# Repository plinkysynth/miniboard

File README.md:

# miniboard - a super minimal fatar tp9 37 key keybed scanner using an rp2040 mcu by @mmalex.bsky.social

August 2026

## the keybed wot you need

there's no point looking at this project until you are the proud owner of a fatar 9s keybed. probably the 37 key variant. 

- the keybed - https://www.fatar.com/products/tp9s/
- datasheet - https://www.antonus-synths.com/enlo-1/fatar/DataSheet-TP9S%2BP.pdf

I got mine at great expense a few years ago from
https://enlo-1.com/products/fatar-tp-9s-keyboard
but im not sure if they are meant to sell them to us hobbyists? either way it was expensive for what it is! maybe you can find one cheaper somewhere else. I am not affiliated with them in any way, just documenting my build.

## whence came this mess

forked from my earlier 2024 zacboard project, that included an oled, 2 encoders, and a silly set of i2c slider boards that allowed it to sport more sliders than keys.

im not sure if i ever released that one publically (* i did not), but i was curious about making a super minimal 'fatar keybed and nothing else' the other day, so I stripped everything down, speed-designed a PCB, and re-ordered from JLC. the boards just arrived, they work, I am putting this up on github before thinking too much...

## software

the software just times make/breaks when scanning the keybed, as one must, and uses that to pick a velocity.

it also feeds the aftertouch resistor to ADC0 and uses that to generate aftertouch events.

it sends MIDI messages out on channel 0 on the TRS port and over usb midi. 

the pcb has a 3 pin connector for a raspberry pi debug probe 

https://www.raspberrypi.com/products/debug-probe/

which I highly recommend for all rp2040 hacking projects. it gives you quick way to flash new software without messing with reset buttons, clean debugging in vscode, watch, breakpoints, etc.

i set this project to use rtt segger style printf, which is THE ONE TRUE WAY but is surprisingly underdocumented in the pico sdk. If you have a probe connected you can
see your printf's in vscode via the TERMINAL tab, and its really cheap, and doesnt tie up the USB port or a 
serial port, nor use any GPIOs. lovely!

## hardware

power is over usb-c obviously

i did this in a yolo rush, so its a bit rough.
ordering your own pcbs, its the usual kicad -> jlcpcb -> yay!
I even left the production files checked in, so you could even just upload those straight to JLC. it worked for me, but see the section below on improvements you might want to make before spending money.

all the parts should be readily available via their assembly service.

I accept no responsibility for anything that may come from building this stuff! you're on your own.

## mounting

the open scad file is for a simple plank to screw onto the keybed and mount the circuit board.

a plank of wood or other material would be nicer.

i screwed it into the keybed with 8 wood screws i found in a cupboard :) M3 or M4 I think they were.
the pcb has two m3 holes in it, which I used 2 M3 machine screws and nuts for. the stl/openscad file has holes for these.

## keybed connector

i HATE HATE HATE the minimatch connector that fatar uses, but here we are. you need some 20 way
ribbon cable to clamp it onto, which requires FORCE which often breaks the fragile plastic.
I got the connectors from digikey:

| use | quantity | digikey part | manufacturer | manufacturer part | description |
| --- | ---: | --- | --- | --- | --- |
| for the cable... | 2x | A99456CT-ND | TE CONNECTIVITY AMP (VA) | 9-215083-0 | CONN PLUG 20POS IDC 28AWG TIN |
| for the pcb... | 1x | A99465CT-ND | TE CONNECTIVITY AMP (VA) | 9-215079-0 | CONN RCPT 20POS 0.1 TIN PCB |

and standard 28AWG 20 way ribbon cable.

The keybed also has a little flat flex variable resistor. connect two wires to it
and solder them to the outer two pins of the 4 pin connector on the pcb. voila,
after touch.

## PCB design mistakes chapter:

* i should have connected the last 2 pins to GPIOs. I didn't. as a result you can't scan larger keyboards.
If i was ordering from JLCPCB again, I'd hook up those two not connected pins to GPIOs.

* the TRS jack for midi is too close to the USB-C. it works, but its close.

* obviously it could sprout more connections, encoders, buttons, etc.... but that wasnt the point of 
this minimalist project.  

* it would make sense to expose more of the free GPIOs as testpads or connectors or whatnot.

* the routing is fine, honest.

## license

released into as liberal a license as I can: [CC0](LICENSE.md)...

- alex 'mmalex' evans august 2026

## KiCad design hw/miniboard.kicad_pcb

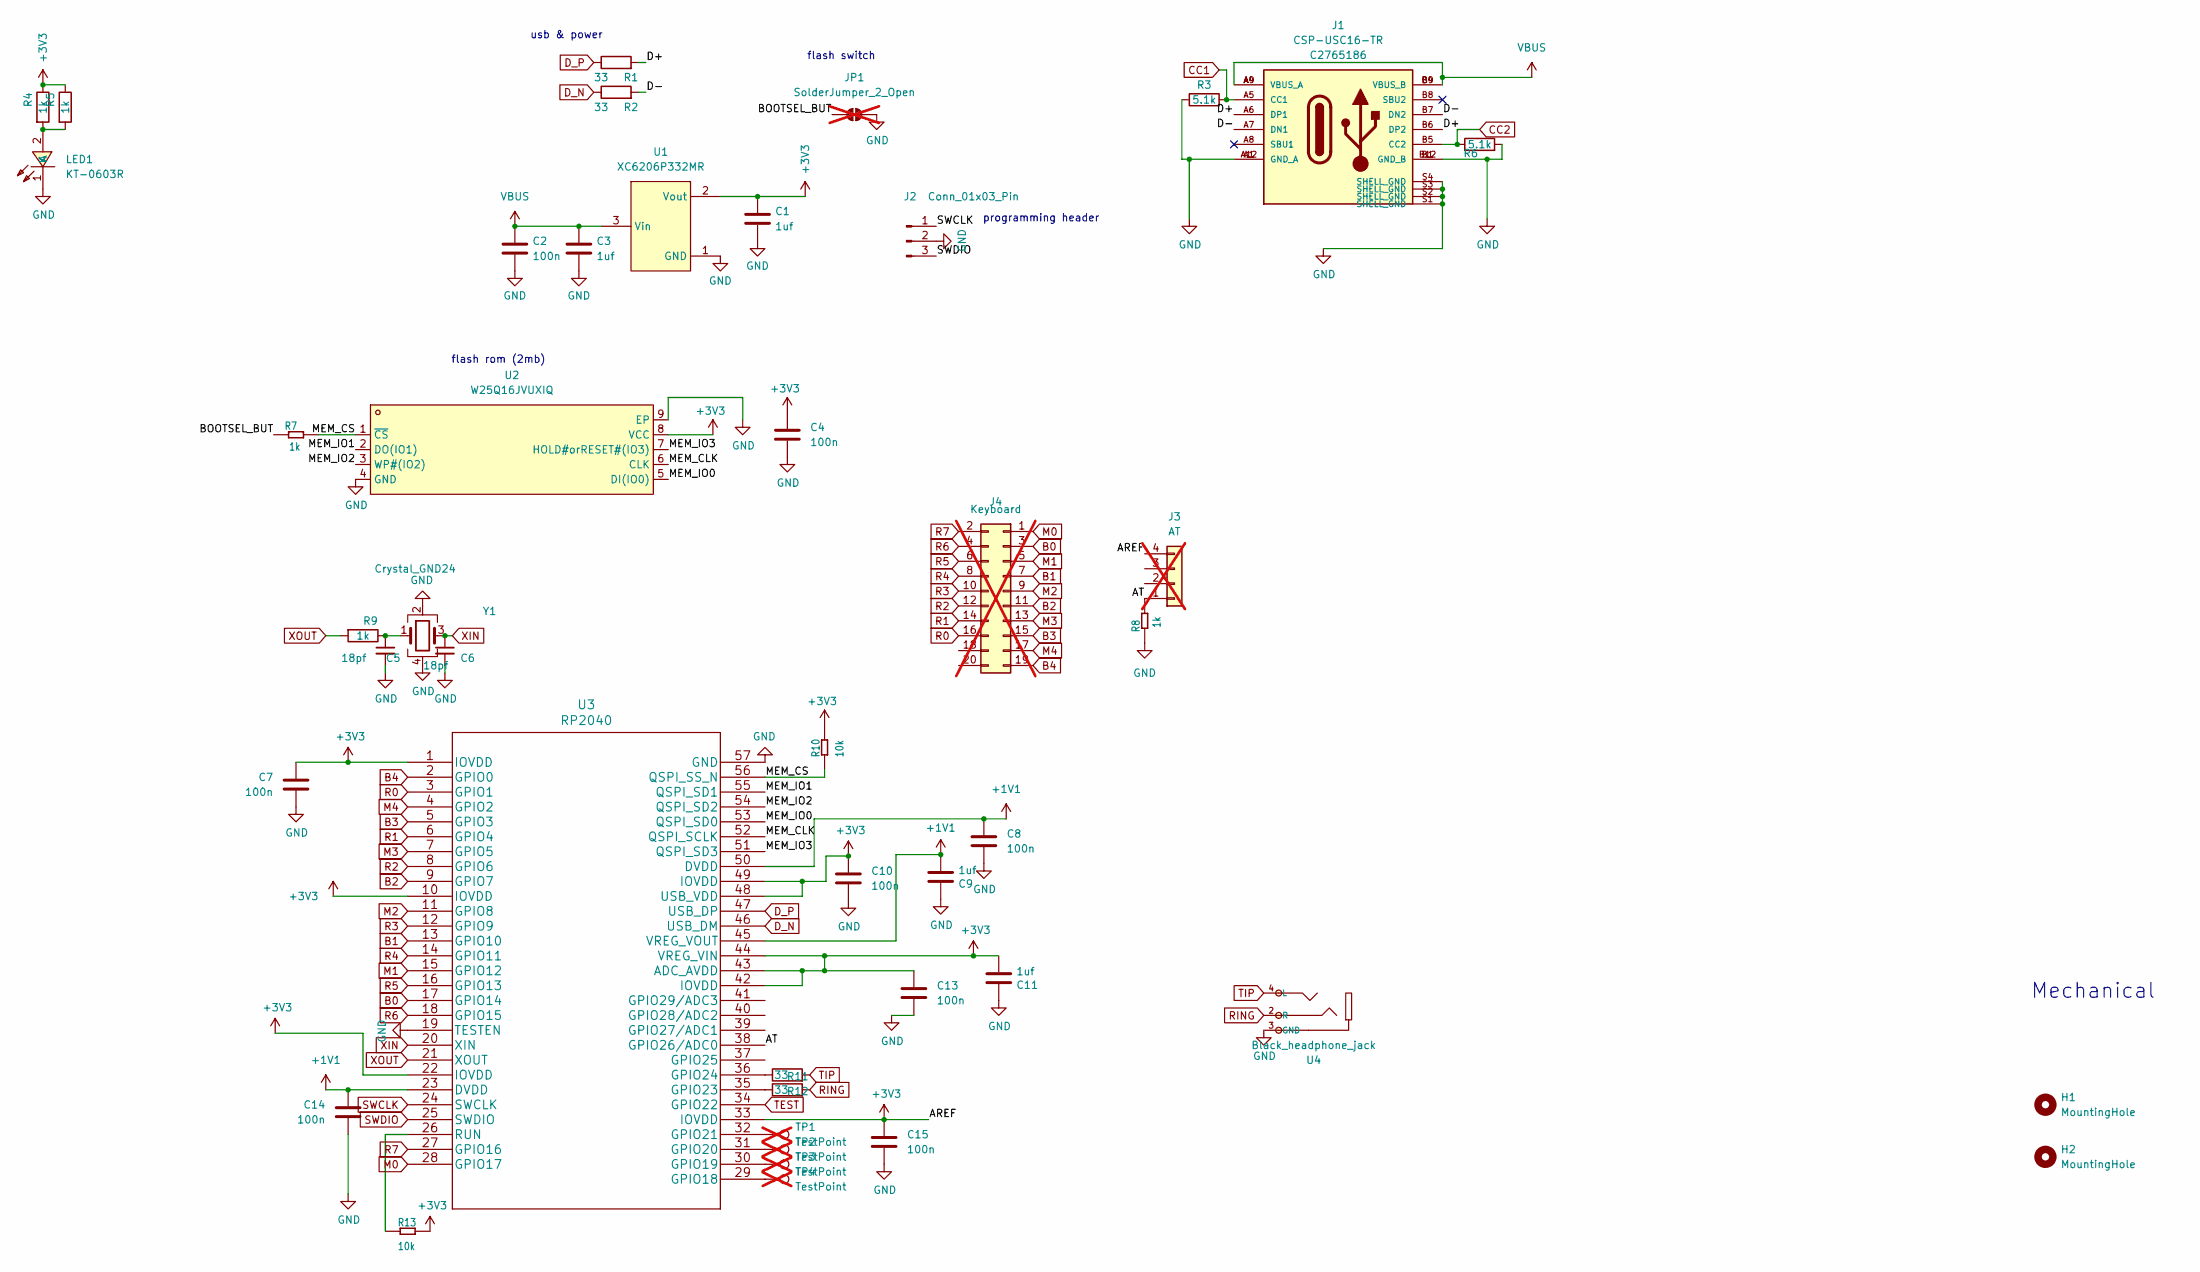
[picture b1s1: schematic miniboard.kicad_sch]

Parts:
C1, C3, C9, C11: 1uf; C_0402_1005Metric; LCSC C52923
C2, C4, C7, C8, C10, C13, C14, C15: 100n; C_0402_1005Metric; LCSC C307331
C5, C6: 18pf; C_0402_1005Metric; LCSC C1549
H1, H2: MountingHole; MountingHole_3.2mm_M3
J1: CSP-USC16-TR; VALCON_CSP-USC16-TR; PARTREV A0; LCSC C2765186
J2: Conn_01x03_Pin; JST_SH_SM03B-SRSS-TB_1x03-1MP_P1.00mm_Horizontal; LCSC C160403
J3: AT; PinHeader_1x04_P2.54mm_Horizontal; not fitted
J4: Keyboard; TE_9-215079-0; not fitted
JP1: SolderJumper_2_Open; SolderJumper-2_P1.3mm_Open_Pad1.0x1.5mm; not fitted
LED1: KT-0603R; LED0603-RD; LCSC Part C2286
R1, R2, R11, R12: 33; R_0402_1005Metric; LCSC C25105
R3, R6: 5.1k; R_0402_1005Metric; LCSC C2906948
R4, R5, R7, R8, R9: 1k; R_0402_1005Metric; LCSC C11702
R10, R13: 10k; R_0402_1005Metric; LCSC C25744
TP1, TP2, TP3, TP4: TestPoint; TestPoint_Pad_1.5x1.5mm; not fitted
U1: XC6206P332MR; SOT-23-3_L2.9-W1.6-P1.90-LS2.8-BR; LCSC Part C5446
U2: W25Q16JVUXIQ; USON-8_L3.0-W2.0-P0.50-BL-EP; LCSC Part C2843335
U3: RP2040; QFN-56-1EP_7x7mm_P0.4mm_EP3.2x3.2mm; LCSC C2040
U4: Black_headphone_jack; AUDIO-TH_PJ-3200; LCSC C2689690
Y1: Crystal_GND24; Crystal_SMD_2520-4Pin_2.5x2.0mm; LCSC C284155

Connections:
+1V1: C8.1, C9.2, C14.1, U3.23 (DVDD), U3.45 (VREG_VOUT), U3.50 (DVDD)
+3V3: C1.1, C4.1, C7.1, C10.1, C11.2, C13.1, C15.1, J3.4, R4.1, R5.1, R10.2, R13.2, U1.2 (Vout), U2.8 (VCC), U3.1 (IOVDD), U3.10 (IOVDD), U3.22 (IOVDD), U3.33 (IOVDD), U3.42 (IOVDD), U3.43 (ADC_AVDD), U3.44 (VREG_VIN), U3.48 (USB_VDD), U3.49 (IOVDD)
/AT: J3.1, R8.2, U3.38 (GPIO26/ADC0)
/BOOTSEL_BUT: JP1.1 (A), R7.1
/D+: J1.A6 (DP1), J1.B6 (DP2), R1.2
/D-: J1.A7 (DN1), J1.B7 (DN2), R2.2
/MEM_CLK: U2.6 (CLK), U3.52 (QSPI_SCLK)
/MEM_CS: R7.2, R10.1, U2.1 (~CS), U3.56 (QSPI_SS_N)
/MEM_IO0: U2.5 (DI(IO0)), U3.53 (QSPI_SD0)
/MEM_IO1: U2.2 (DO(IO1)), U3.55 (QSPI_SD1)
/MEM_IO2: U2.3 (WP#(IO2)), U3.54 (QSPI_SD2)
/MEM_IO3: U2.7 (HOLD#orRESET#(IO3)), U3.51 (QSPI_SD3)
B0: J4.3, U3.17 (GPIO14)
B1: J4.7, U3.13 (GPIO10)
B2: J4.11, U3.9 (GPIO7)
B3: J4.15, U3.5 (GPIO3)
B4: J4.19, U3.2 (GPIO0)
CC1: J1.A5 (CC1), R3.2
CC2: J1.B5 (CC2), R6.1
D_N: R2.1, U3.46 (USB_DM)
D_P: R1.1, U3.47 (USB_DP)
GND: C1.2, C2.2, C3.2, C4.2, C5.2, C6.2, C7.2, C8.2, C9.1, C10.2, C11.1, C13.2, C14.2, C15.2, J1.A1 (GND_A), J1.A12 (GND_A), J1.B1 (GND_B), J1.B12 (GND_B), J1.S1 (SHELL_GND), J1.S2 (SHELL_GND), J1.S3 (SHELL_GND), J1.S4 (SHELL_GND), J2.2, JP1.2 (B), LED1.1 (K), R3.1, R6.2, R8.1, U1.1 (GND), U2.4 (GND), U2.9 (EP), U3.19 (TESTEN), U3.57 (GND), U4.3 (GND), Y1.2, Y1.4
M0: J4.1, U3.28 (GPIO17)
M1: J4.5, U3.15 (GPIO12)
M2: J4.9, U3.11 (GPIO8)
M3: J4.13, U3.7 (GPIO5)
M4: J4.17, U3.4 (GPIO2)
unnamed: C5.1, R9.1, Y1.1
unnamed: LED1.2 (A), R4.2, R5.2
unnamed: TP4.1, U3.29 (GPIO18)
unnamed: TP3.1, U3.30 (GPIO19)
unnamed: TP2.1, U3.31 (GPIO20)
unnamed: TP1.1, U3.32 (GPIO21)
unnamed: R12.1, U3.35 (GPIO23)
unnamed: R11.1, U3.36 (GPIO24)
unnamed: R13.1, U3.26 (RUN)
R0: J4.16, U3.3 (GPIO1)
R1: J4.14, U3.6 (GPIO4)
R2: J4.12, U3.8 (GPIO6)
R3: J4.10, U3.12 (GPIO9)
R4: J4.8, U3.14 (GPIO11)
R5: J4.6, U3.16 (GPIO13)
R6: J4.4, U3.18 (GPIO15)
R7: J4.2, U3.27 (GPIO16)
RING: R12.2, U4.2 (R)
SWCLK: J2.1, U3.24 (SWCLK)
SWDIO: J2.3, U3.25 (SWDIO)
TEST: U3.34 (GPIO22)
TIP: R11.2, U4.4 (L)
VBUS: C2.1, C3.1, J1.A4 (VBUS_A), J1.A9 (VBUS_A), J1.B4 (VBUS_B), J1.B9 (VBUS_B), U1.3 (Vin)
XIN: C6.1, U3.20 (XIN), Y1.3
XOUT: R9.2, U3.21 (XOUT)

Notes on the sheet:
programming header
Mechanical
usb & power
flash switch
flash rom (2mb)

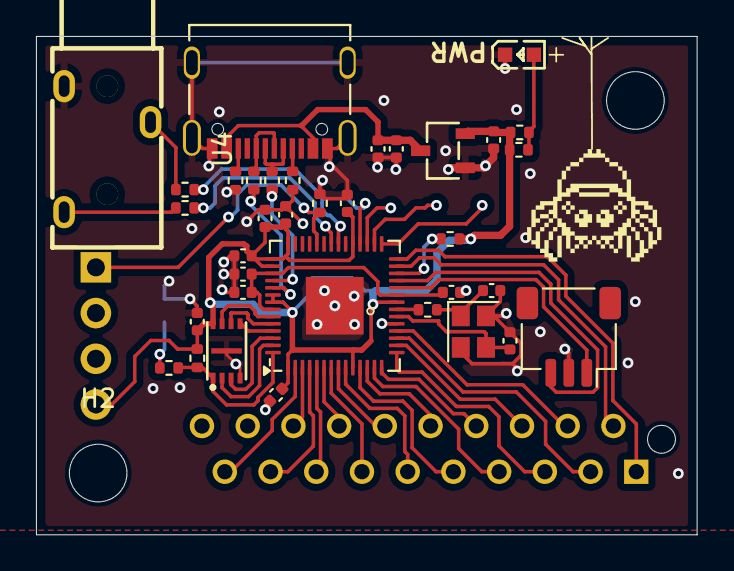
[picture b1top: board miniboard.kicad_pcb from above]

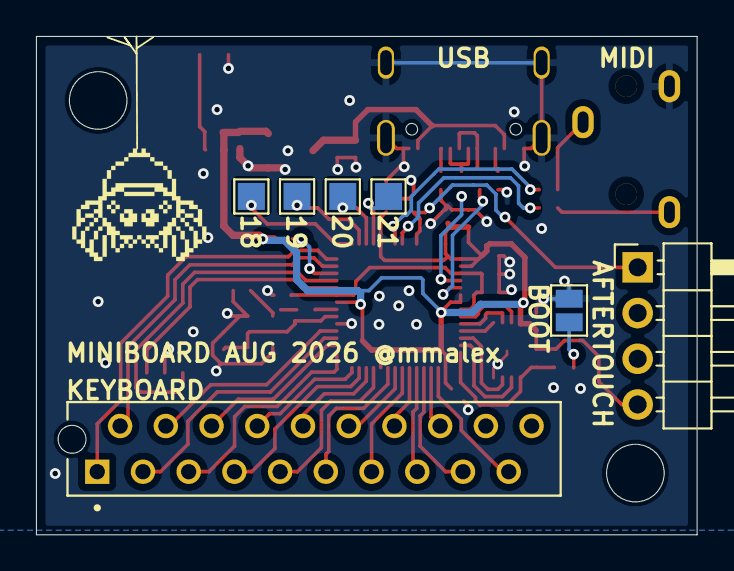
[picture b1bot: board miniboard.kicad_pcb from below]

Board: 2 copper layers, 36.7 x 27.7 mm, 44 parts (7 on the bottom side), 51 nets.

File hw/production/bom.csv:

Designator,Footprint,Quantity,Value,LCSC Part #
"C1, C11, C3, C9",0402,4,1uf,C52923
"C10, C13, C14, C15, C2, C4, C7, C8",0402,8,100n,C307331
"C5, C6",0402,2,18pf,C1549
"H1, H2",MountingHole_3.2mm_M3,2,MountingHole,
J1,VALCON_CSP-USC16-TR,1,CSP-USC16-TR,C2765186
J2,JST_SH_SM03B-SRSS-TB_1x03-1MP_P1.00mm_Horizontal,1,Conn_01x03_Pin,C160403
LED1,LED0603-RD,1,KT-0603R,C2286
"R1, R11, R12, R2",0402,4,33,C25105
"R10, R13",0402,2,10k,C25744
"R3, R6",0402,2,5.1k,C2906948
"R4, R5, R7, R8, R9",0402,5,1k,C11702
U1,SOT-23-3_L2.9-W1.6-P1.90-LS2.8-BR,1,XC6206P332MR,C5446
U2,USON-8_L3.0-W2.0-P0.50-BL-EP,1,W25Q16JVUXIQ,C2843335
U3,QFN-56-1EP_7x7mm_P0.4mm_EP3.2x3.2mm,1,RP2040,C2040
U4,AUDIO-TH_PJ-3200,1,Black_headphone_jack,C2689690
Y1,Crystal_SMD_2520-4Pin_2.5x2.0mm,1,Crystal_GND24,C284155
